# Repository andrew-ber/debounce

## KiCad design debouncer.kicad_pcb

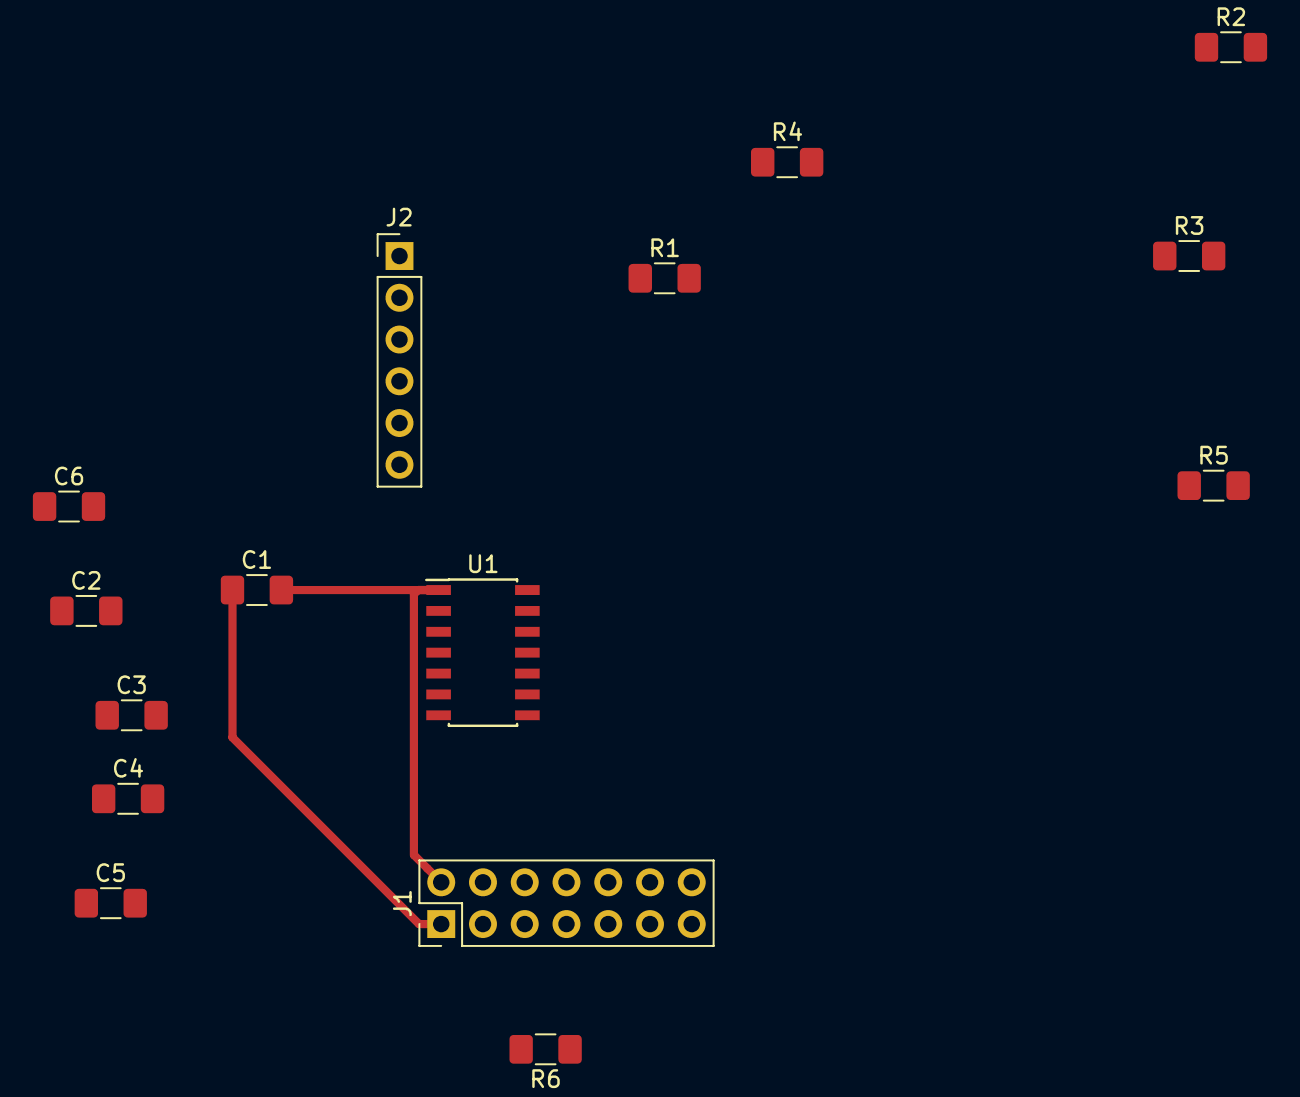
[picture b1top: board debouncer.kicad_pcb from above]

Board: 2 copper layers, 15 parts (0 on the bottom side), 20 nets.

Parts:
C1, C2, C3, C4, C5, C6: C100p; C_1206_3216Metric_Pad1.42x1.75mm_HandSolder
J1: Conn_02x07_Row_Letter_Last; PinHeader_2x07_P2.54mm_Vertical
J2: Conn_01x06_Male; PinHeader_1x06_P2.54mm_Vertical
R1, R2, R3, R4, R5, R6: R10K; R_1206_3216Metric_Pad1.42x1.75mm_HandSolder
U1: 74HC14; SOIC-14_3.9x8.7mm_P1.27mm

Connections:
GND: J1.14, R1.1, R2.1, R3.1, R4.1, R5.2, R6.2, U1.7
unnamed: C1.1, J1.1
unnamed: C1.2, J1.2, R1.2, U1.1
unnamed: C2.1, J1.3
unnamed: C2.2, J1.4, R2.2, U1.3
unnamed: C3.1, J1.5
unnamed: C3.2, J1.6, R3.2, U1.5
unnamed: C4.1, J1.7
unnamed: C4.2, J1.8, R4.2, U1.9
unnamed: C5.1, J1.9
unnamed: C5.2, J1.10, R5.1, U1.11
unnamed: C6.1, J1.11
unnamed: C6.2, J1.12, R6.1, U1.13
unnamed: J2.1, U1.2
unnamed: J2.2, U1.4
unnamed: J2.3, U1.6
unnamed: J2.4, U1.8
unnamed: J2.5, U1.10
unnamed: J2.6, U1.12
VDC: J1.13, U1.14

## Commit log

2018-10-05 init
2018-10-05 05-10
